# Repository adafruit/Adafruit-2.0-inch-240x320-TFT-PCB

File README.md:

## Adafruit 2.0" 320x240 Color IPS TFT Display with microSD Card Breakout PCB

<a href="http://www.adafruit.com/products/4311"><br/>
Click here to purchase one from the Adafruit shop</a>

PCB files for the Adafruit 2.0" 320x240 Color IPS TFT Display with microSD Card Breakout. 

Format is EagleCAD schematic and board layout
* https://www.adafruit.com/product/4311

### Description

This gorgeous IPS display breakout is the best way to add a small, colorful, and bright display to any project, with excellent visibility from any angle. Since the display uses 4-wire SPI to communicate and has its own pixel-addressable frame buffer, it can be used with every kind of microcontroller. Even a very small one with low memory and few pins available!

The 2.0" display has 320x240 color pixels. Unlike the low cost "Nokia 6110" and similar LCD displays, which are CSTN type and thus have poor color and slow refresh, this display is a true TFT! Not only that, but its an IPS display for vivid color and high-angle visibility. The TFT driver (ST7789) can display full 18-bit color (262,144 shades), but almost all drivers will use just 16-bit color. The TFT will always come with the same driver chip so there's no worries that your code will not work from one to the other.

The breakout has the TFT display soldered on (it uses a delicate flex-circuit connector) as well as a ultra-low-dropout 3.3V regulator, auto-reset circuitry, and a 3/5V level shifter so you can use it with 3.3V or 5V power and logic. We also had a little space so we placed a microSD card holder so you can easily load full color bitmaps from a FAT16/FAT32 formatted microSD card. The microSD card is not included, but you can pick one up here.

Of course, we wouldn't just leave you with a datasheet and a "good luck!" - we've written a full open source graphics library that can draw pixels, lines, rectangles, circles, text, and bitmaps as well as example code. The code is written for Arduino but can be easily ported to your favorite microcontroller! Wiring is easy, we strongly encourage using the hardware SPI pins of your Arduino as software SPI is noticeably slower when dealing with this size display.

New! As of February 2023, this display breakout also features an 18-pin "EYESPI" standard FPC connector with flip-top connector. You can use an 18-pin 0.5mm pitch FPC cable to connect to the display over SPI and I2C, respectively. Great for when you want to skip soldering all those headers. 

### License

Adafruit invests time and resources providing this open source design, please support Adafruit and open-source hardware by purchasing products from [Adafruit](https://www.adafruit.com)!

Designed by Limor Fried/Ladyada for Adafruit Industries.

Creative Commons Attribution/Share-Alike, all text above must be included in any redistribution. 
See license.txt for additional details.

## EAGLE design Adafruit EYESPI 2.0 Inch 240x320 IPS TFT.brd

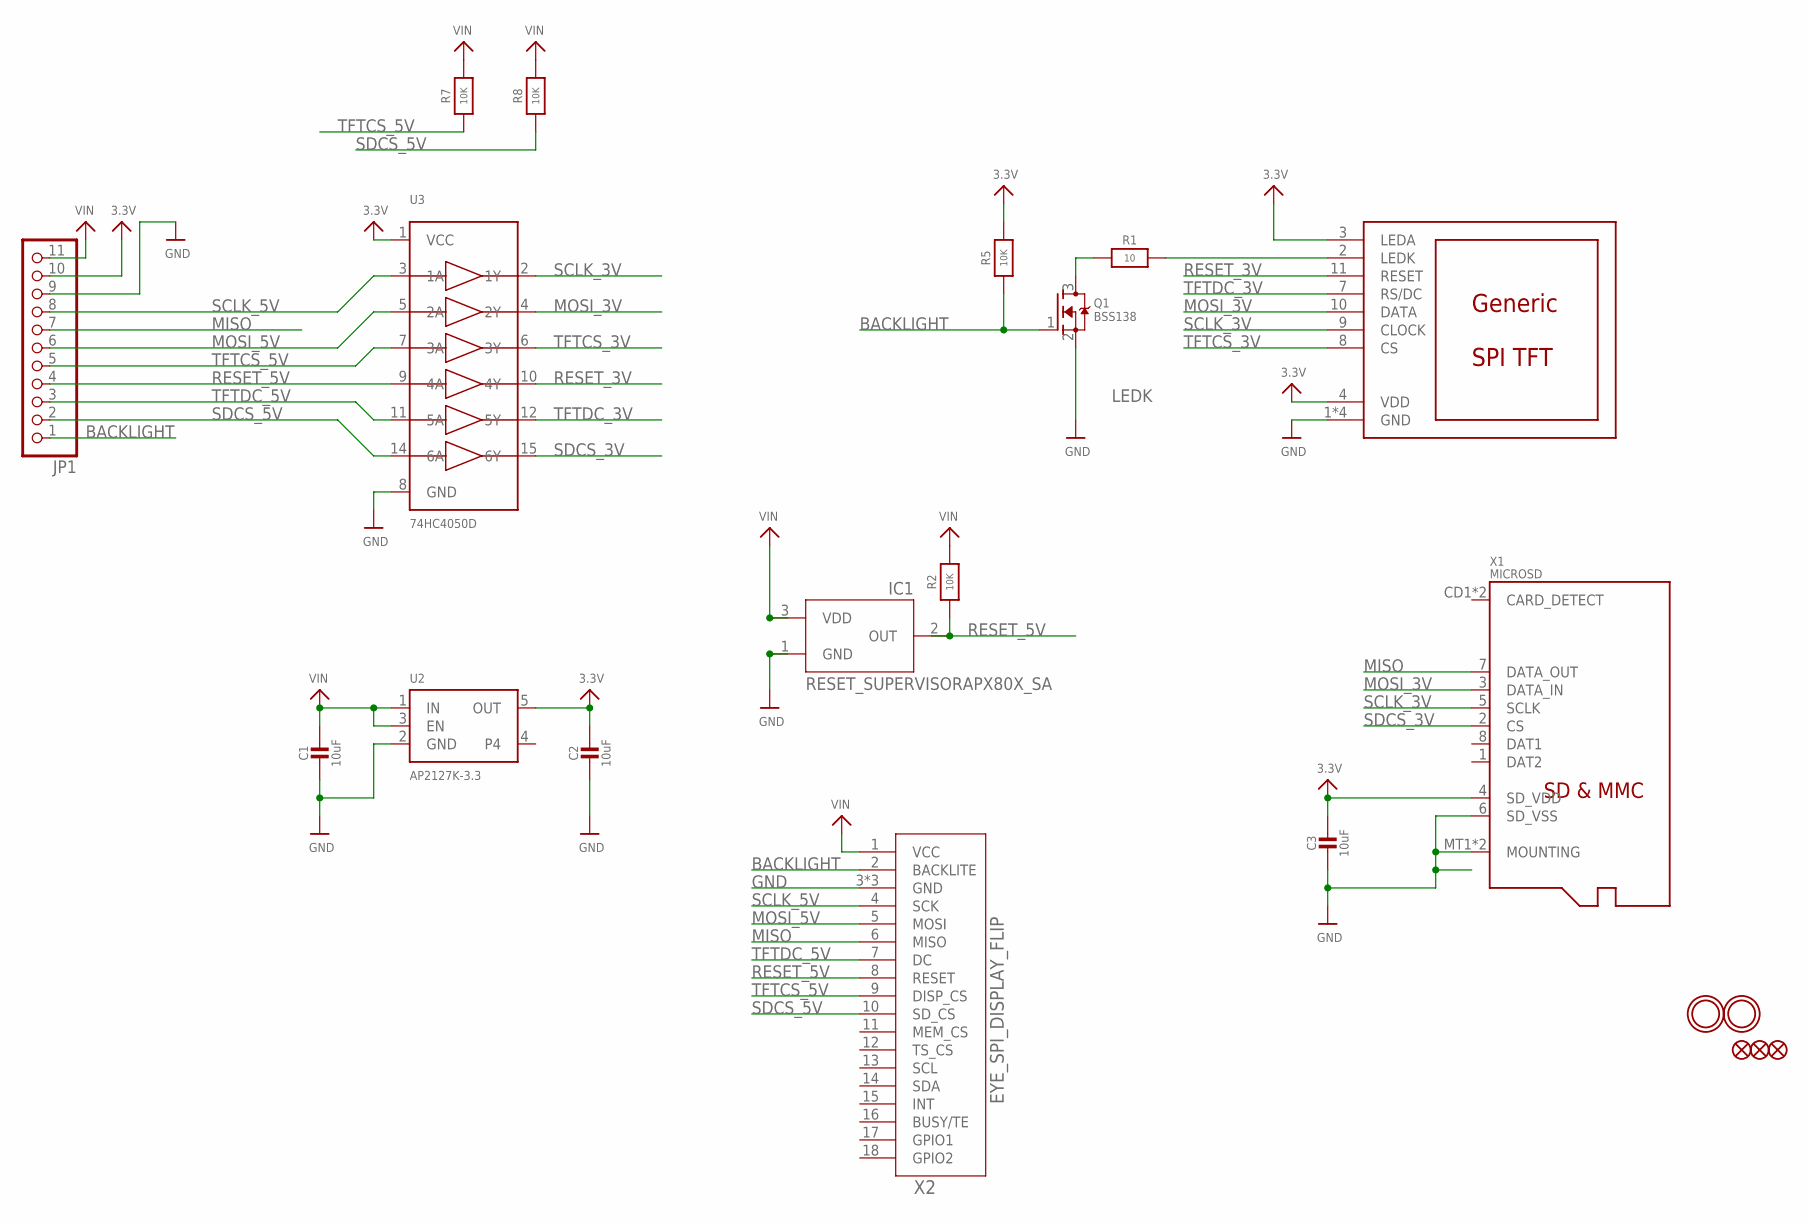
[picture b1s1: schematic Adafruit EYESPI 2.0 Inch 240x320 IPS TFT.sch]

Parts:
C1, C2, C3: 10uF; 0805-NO
DISP1: DISP_LCD_GENERIC_SPI_2.0IN_240X320; TFT_2.0IN_240X320_12P
FID1, FID2, FID3: FIDUCIAL_1MM
IC1: RESET_SUPERVISORAPX80X_SA; SOT23-WIDE
JP1: HEADER-1X1176MIL; 1X11_ROUND_76
Q1: BSS138; SOT23-R
R1: 10; 0805-NO
R2, R5, R7, R8: 10K; 0805-NO
U2: AP2127K-3.3; SOT23-5
U3: 74HC4050D; SOIC16
U$3, U$4: MOUNTINGHOLE2.5; MOUNTINGHOLE_2.5_PLATED
X1: MICROSD
X2: EYE_SPI_DISPLAY_FLIP; EYE_SPI_DISPLAY_BOTCONTACT

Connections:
3.3V: C2.1, C3.1, DISP1.3 (LEDA), DISP1.4 (VDD), JP1.10, R5.2, U2.5 (OUT), U3.1 (VCC), X1.4 (SD_VDD)
BACKLIGHT: JP1.1, Q1.1 (G), R5.1, X2.2 (BACKLITE)
GND: C1.2, C2.2, C3.2, DISP1.1 (GND), DISP1.5 (GND), DISP1.6 (GND), DISP1.12 (GND), IC1.1 (GND), JP1.9, Q1.2 (S), U2.2 (GND), U3.8 (GND), X1.6 (SD_VSS), X1.MT1 (MOUNTING), X1.MT2 (MOUNTING), X2.3 (GND), X2.SUPPORT1 (GND), X2.SUPPORT2 (GND)
LEDK: Q1.3 (D), R1.1
MISO: JP1.7, X1.7 (DATA_OUT), X2.6 (MISO)
MOSI_3V: DISP1.10 (DATA), U3.4 (2Y), X1.3 (DATA_IN)
MOSI_5V: JP1.6, U3.5 (2A), X2.5 (MOSI)
unnamed: DISP1.2 (LEDK), R1.2
RESET_3V: DISP1.11 (RESET), U3.10 (4Y)
RESET_5V: IC1.2 (OUT), JP1.4, R2.1, U3.9 (4A), X2.8 (RESET)
SCLK_3V: DISP1.9 (CLOCK), U3.2 (1Y), X1.5 (SCLK)
SCLK_5V: JP1.8, U3.3 (1A), X2.4 (SCK)
SDCS_3V: U3.15 (6Y), X1.2 (CS)
SDCS_5V: JP1.2, R8.1, U3.14 (6A), X2.10 (SD_CS)
TFTCS_3V: DISP1.8 (CS), U3.6 (3Y)
TFTCS_5V: JP1.5, R7.1, U3.7 (3A), X2.9 (DISP_CS)
TFTDC_3V: DISP1.7 (RS/DC), U3.12 (5Y)
TFTDC_5V: JP1.3, U3.11 (5A), X2.7 (DC)
VIN: C1.1, IC1.3 (VDD), JP1.11, R2.2, R7.2, R8.2, U2.1 (IN), U2.3 (EN), X2.1 (VCC)

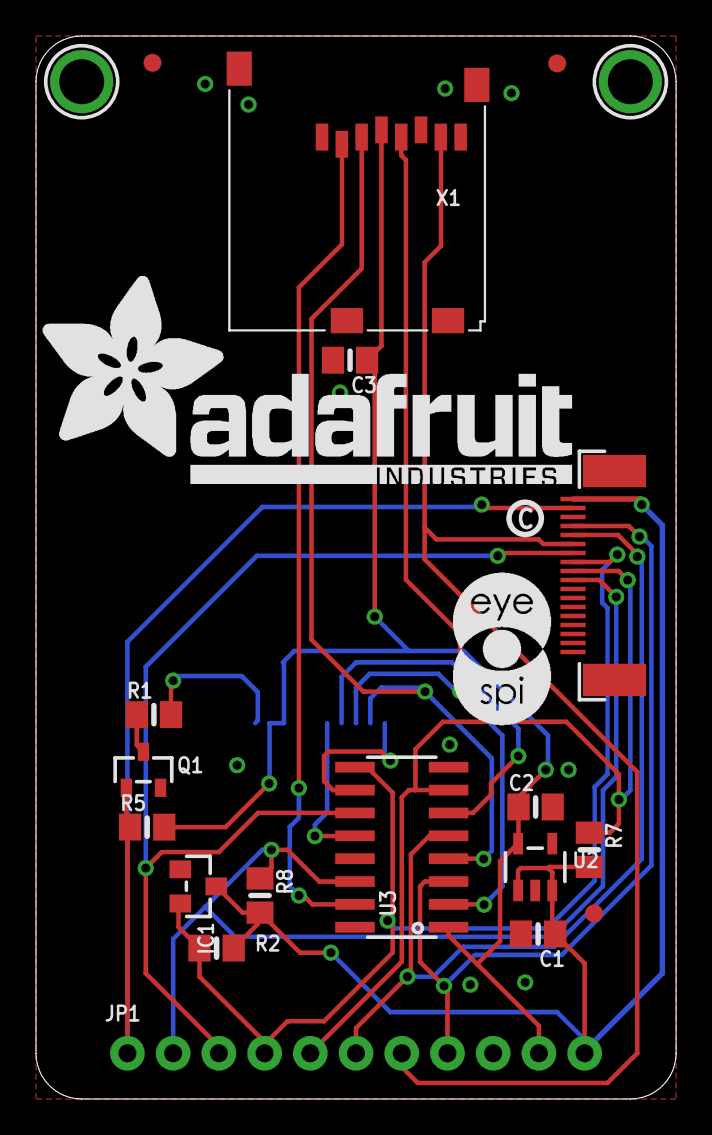
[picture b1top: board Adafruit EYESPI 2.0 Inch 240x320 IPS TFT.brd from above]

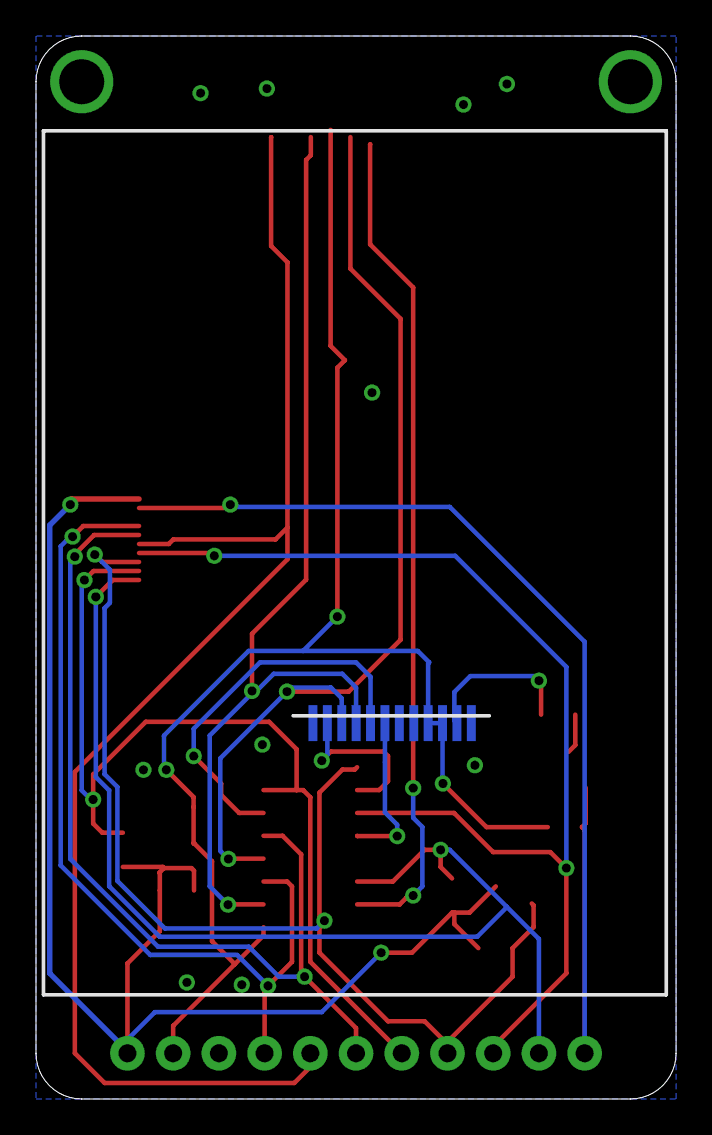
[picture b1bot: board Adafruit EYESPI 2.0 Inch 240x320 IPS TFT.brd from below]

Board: 2 copper layers, 35.6 x 59.1 mm, 48 parts (13 on the bottom side), 19 nets.

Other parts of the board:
PLABEL0: PLABEL0
PLABEL1: PLABEL1
PLABEL2: PLABEL2
PLABEL3: PLABEL3
PLABEL4: PLABEL4
PLABEL5: PLABEL5
PLABEL6: PLABEL6
PLABEL7: PLABEL7
PLABEL8: PLABEL8
PLABEL9: PLABEL9
PLABEL10: PLABEL10
PLABEL11: PLABEL11
PLABEL12: PLABEL12
PLABEL13: PLABEL13
PLABEL14: PLABEL14
PLABEL15: PLABEL15
PLABEL16: PLABEL16
PLABEL17: PLABEL17
PLABEL18: PLABEL18
PLABEL19: PLABEL19
PLABEL20: PLABEL20
PLABEL21: PLABEL21
PLABEL22: PLABEL22
PLABEL23: PLABEL23
U$20: ADAFRUIT_TEXT_30MM
U$24: PCBFEAT-REV-040
U$28: EYESPI_MINI_LOGO

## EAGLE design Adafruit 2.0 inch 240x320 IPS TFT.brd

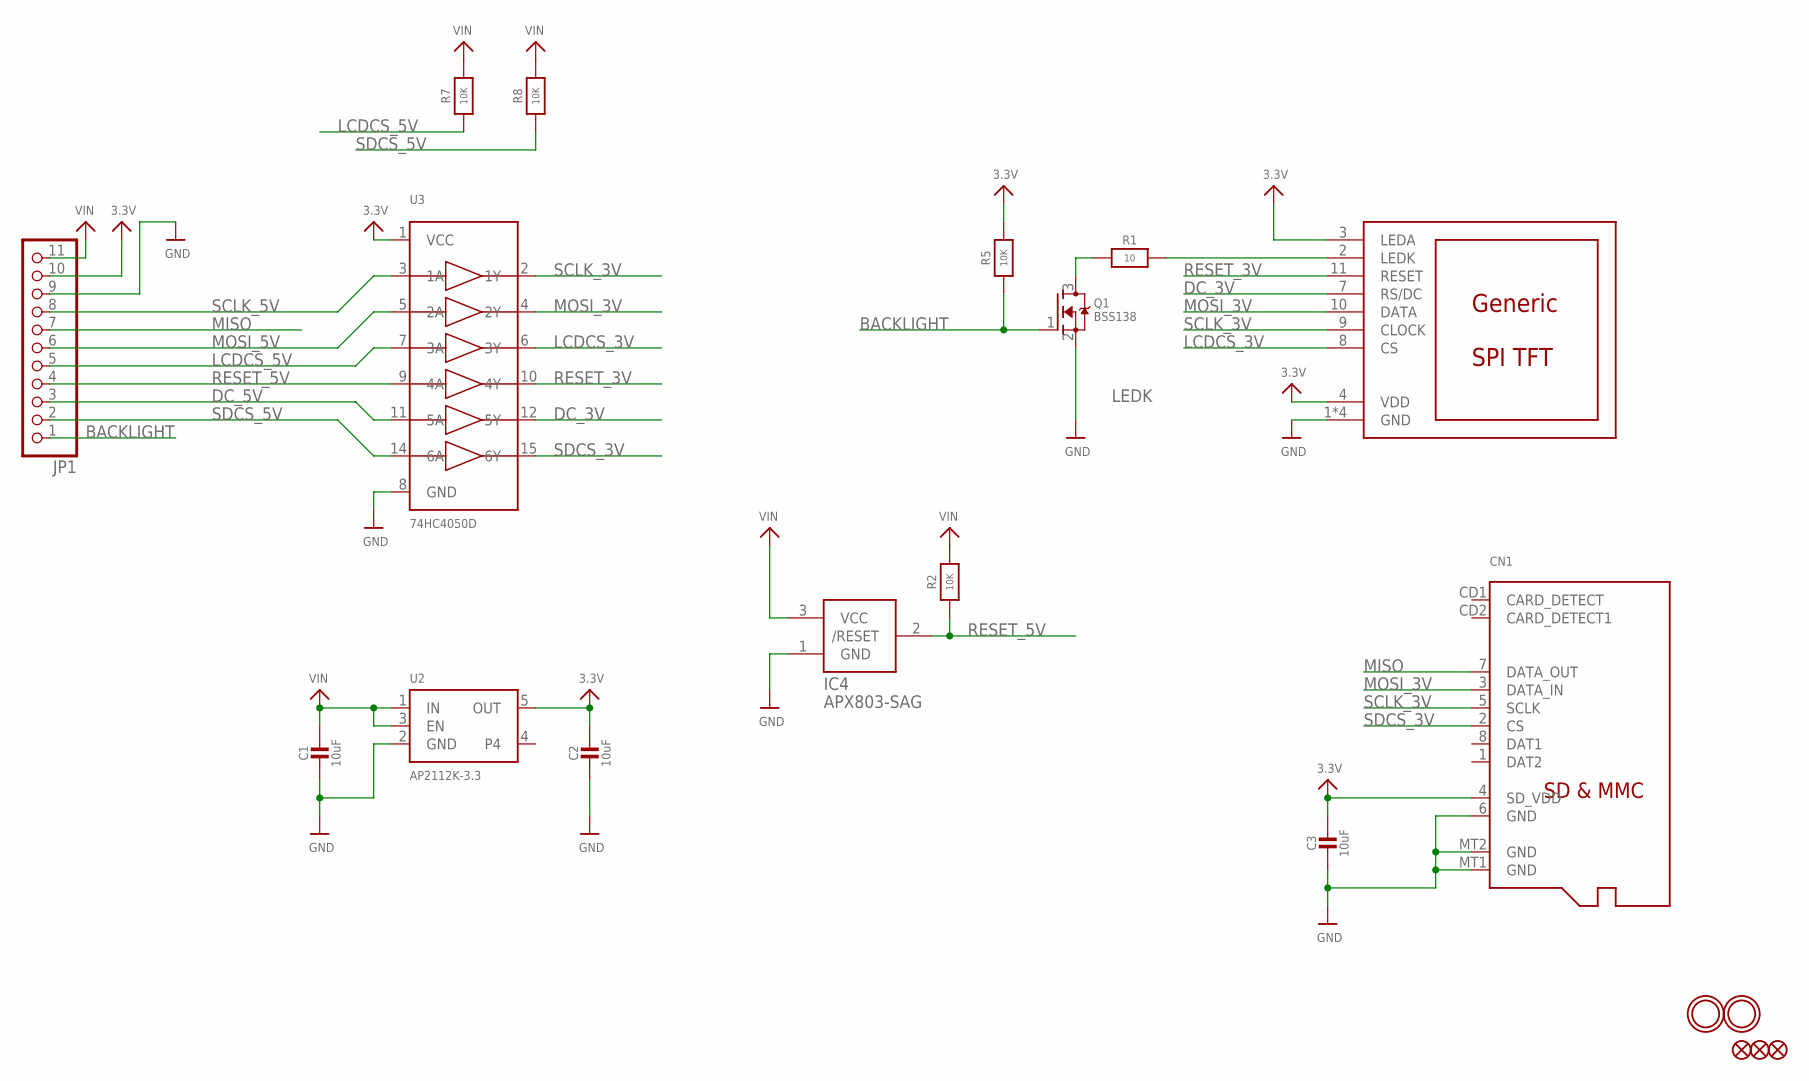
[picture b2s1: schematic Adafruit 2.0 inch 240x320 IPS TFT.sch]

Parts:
C1, C2, C3: 10uF; 0805-NO
CN1: MICROSD
DISP1: DISP_LCD_GENERIC_SPI_2.0IN_240X320; TFT_2.0IN_240X320_12P
FID1, FID2, FID3: FIDUCIAL_1MM
IC4: APX803-SAG; SOT23
JP1: HEADER-1X1176MIL; 1X11_ROUND_76
Q1: BSS138; SOT23-R
R1: 10; 0805-NO
R2, R5, R7, R8: 10K; 0805-NO
U2: AP2112K-3.3; SOT23-5
U3: 74HC4050D; SOIC16
U$3, U$4: MOUNTINGHOLE2.5; MOUNTINGHOLE_2.5_PLATED

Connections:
3.3V: C2.1, C3.1, CN1.4 (SD_VDD), DISP1.3 (LEDA), DISP1.4 (VDD), JP1.10, R5.2, U2.5 (OUT), U3.1 (VCC)
BACKLIGHT: JP1.1, Q1.1 (G), R5.1
DC_3V: DISP1.7 (RS/DC), U3.12 (5Y)
DC_5V: JP1.3, U3.11 (5A)
GND: C1.2, C2.2, C3.2, CN1.6 (GND), CN1.MT1 (GND), CN1.MT2 (GND), DISP1.1 (GND), DISP1.5 (GND), DISP1.6 (GND), DISP1.12 (GND), IC4.1 (GND), JP1.9, Q1.2 (S), U2.2 (GND), U3.8 (GND)
LCDCS_3V: DISP1.8 (CS), U3.6 (3Y)
LCDCS_5V: JP1.5, R7.1, U3.7 (3A)
LEDK: Q1.3 (D), R1.1
MISO: CN1.7 (DATA_OUT), JP1.7
MOSI_3V: CN1.3 (DATA_IN), DISP1.10 (DATA), U3.4 (2Y)
MOSI_5V: JP1.6, U3.5 (2A)
unnamed: DISP1.2 (LEDK), R1.2
RESET_3V: DISP1.11 (RESET), U3.10 (4Y)
RESET_5V: IC4.2 (/RESET), JP1.4, R2.1, U3.9 (4A)
SCLK_3V: CN1.5 (SCLK), DISP1.9 (CLOCK), U3.2 (1Y)
SCLK_5V: JP1.8, U3.3 (1A)
SDCS_3V: CN1.2 (CS), U3.15 (6Y)
SDCS_5V: JP1.2, R8.1, U3.14 (6A)
VIN: C1.1, IC4.3 (VCC), JP1.11, R2.2, R7.2, R8.2, U2.1 (IN), U2.3 (EN)

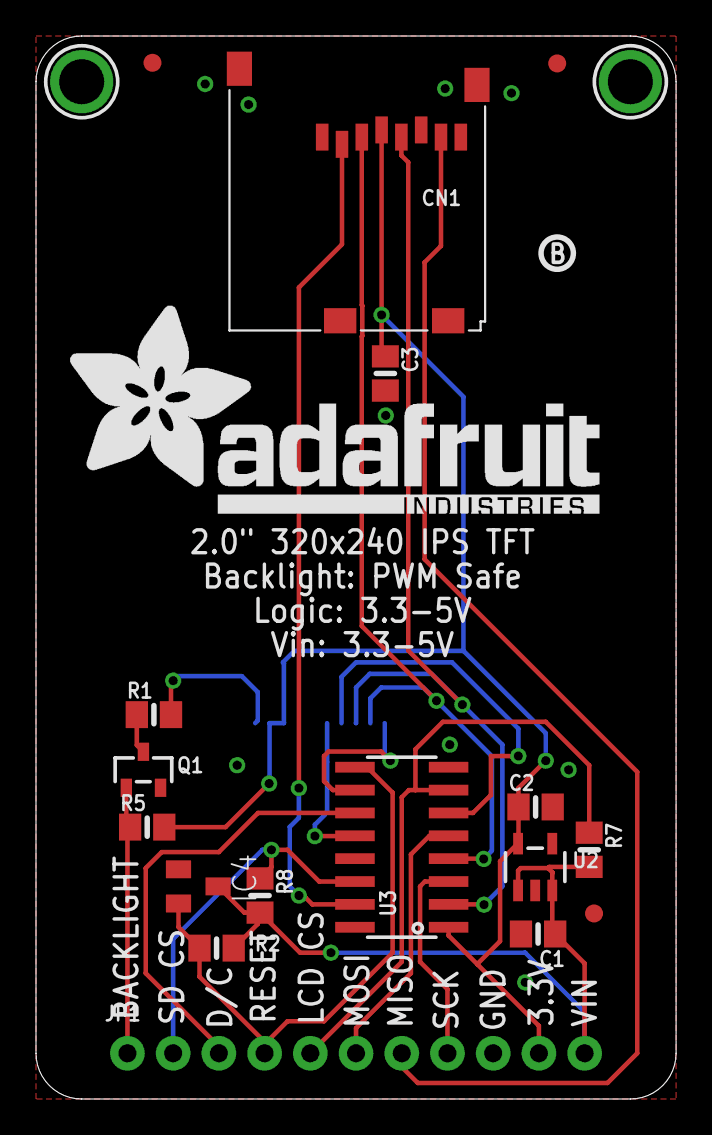
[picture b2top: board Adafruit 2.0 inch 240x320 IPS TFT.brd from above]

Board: 2 copper layers, 35.6 x 59.1 mm, 22 parts (1 on the bottom side), 19 nets.

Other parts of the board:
U$20: ADAFRUIT_TEXT_30MM
U$24: PCBFEAT-REV-040

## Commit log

2019-08-08 Adding board/repo files.
2023-03-02 adding EYESPI files and updating readme
